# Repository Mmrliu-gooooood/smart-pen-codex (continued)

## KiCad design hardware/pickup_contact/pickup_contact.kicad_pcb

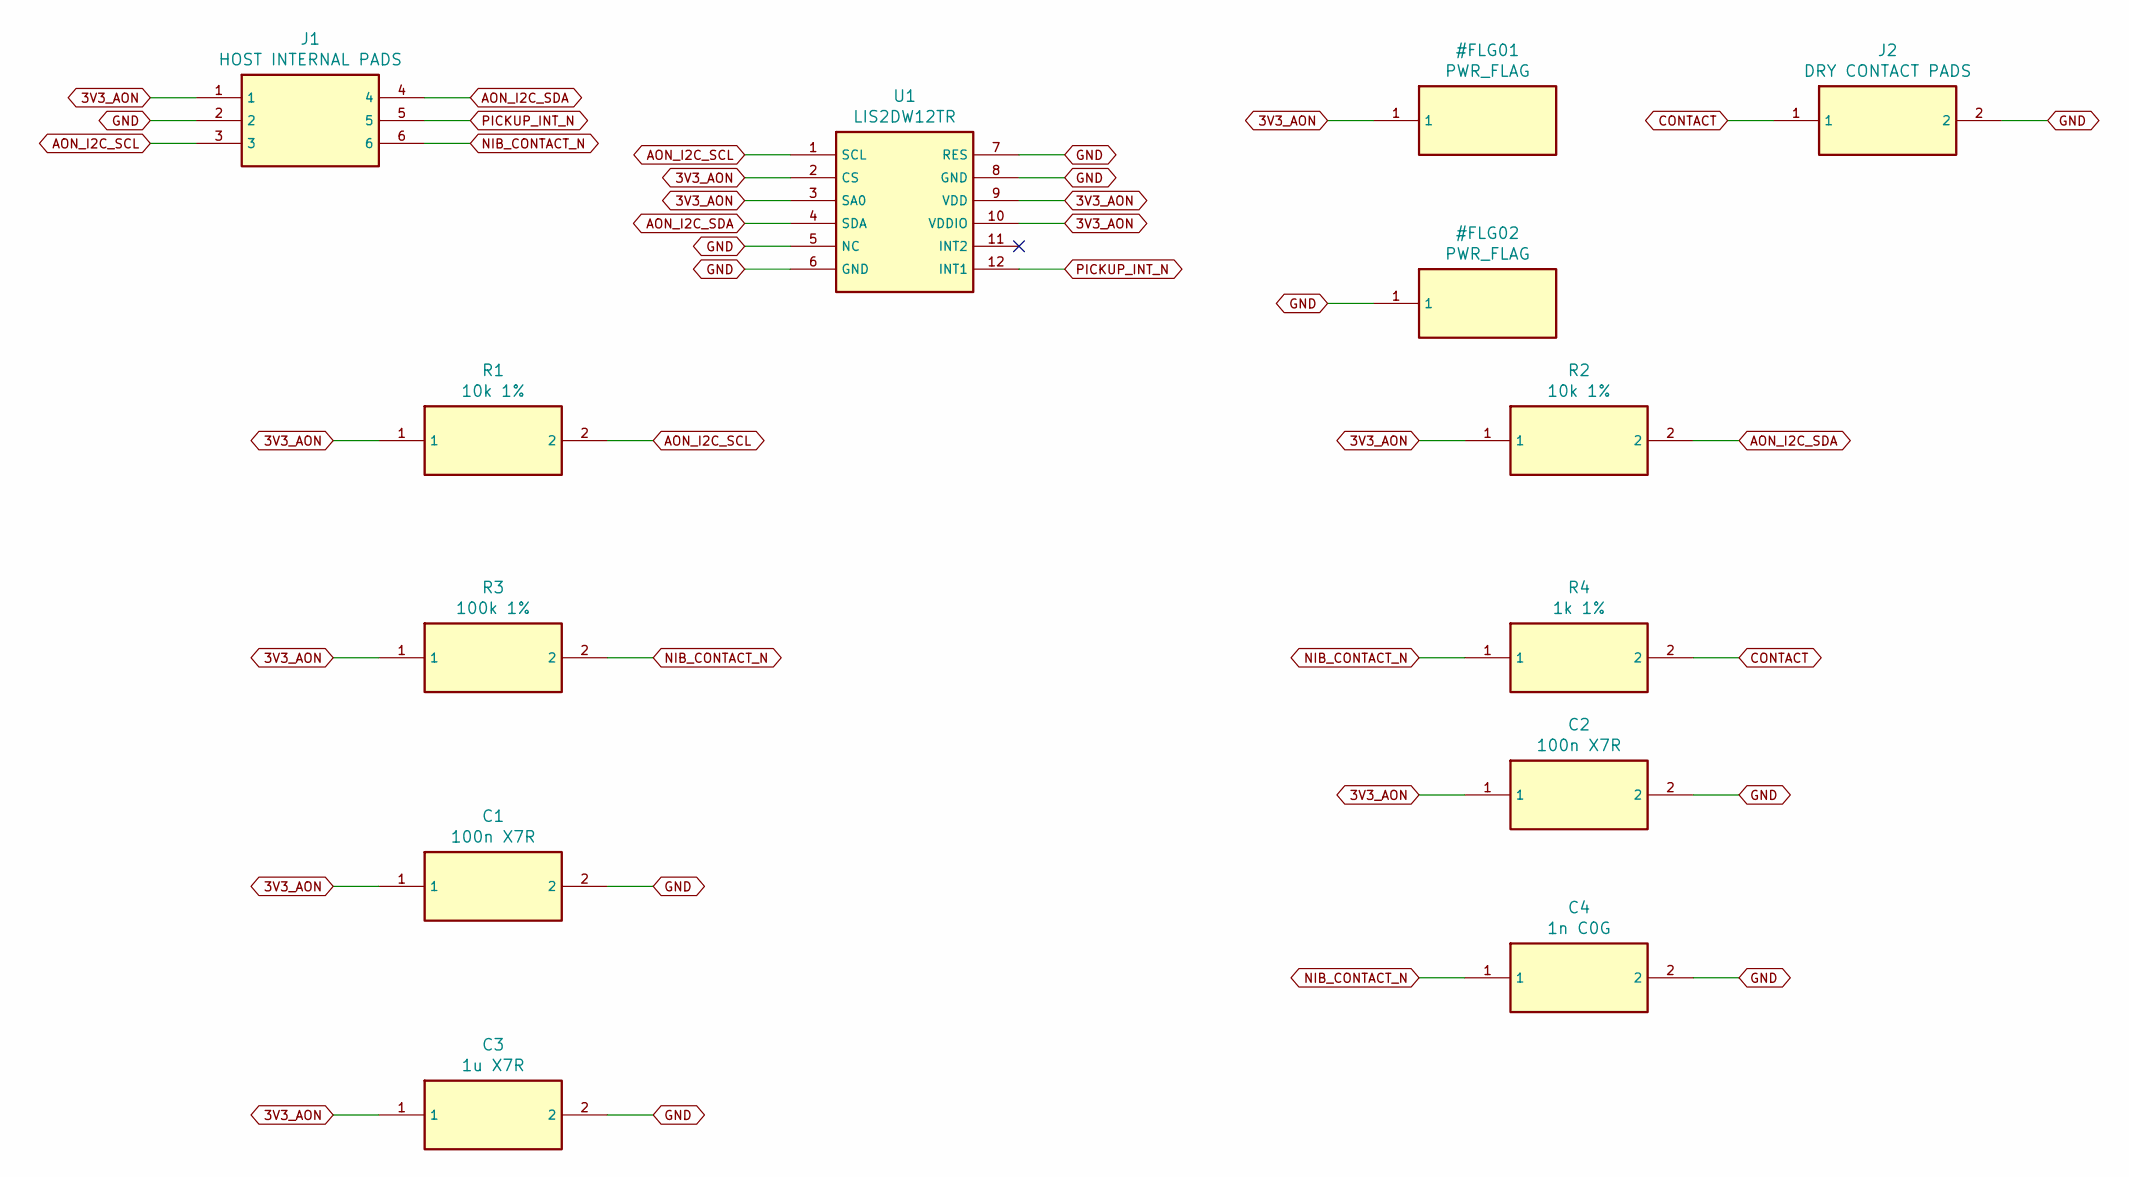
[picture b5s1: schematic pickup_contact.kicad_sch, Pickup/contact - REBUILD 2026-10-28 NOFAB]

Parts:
C1, C2: 100n X7R; C_0603_1608Metric
C3: 1u X7R; C_0603_1608Metric
C4: 1n C0G; C_0603_1608Metric
J1: HOST INTERNAL PADS; Host_6
J2: DRY CONTACT PADS; Contact_2
R1, R2: 10k 1%; R_0603_1608Metric
R3: 100k 1%; R_0603_1608Metric
R4: 1k 1%; R_0603_1608Metric
U1: LIS2DW12TR; LGA-12_2x2mm_P0.5mm

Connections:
3V3_AON: C1.1, C2.1, C3.1, J1.1, R1.1, R2.1, R3.1, U1.2 (CS), U1.3 (SA0), U1.9 (VDD), U1.10 (VDDIO)
AON_I2C_SCL: J1.3, R1.2, U1.1 (SCL)
AON_I2C_SDA: J1.4, R2.2, U1.4 (SDA)
CONTACT: J2.1, R4.2
GND: C1.2, C2.2, C3.2, C4.2, J1.2, J2.2, U1.5 (NC), U1.6 (GND), U1.7 (RES), U1.8 (GND)
NIB_CONTACT_N: C4.1, J1.6, R3.2, R4.1
PICKUP_INT_N: J1.5, U1.12 (INT1)

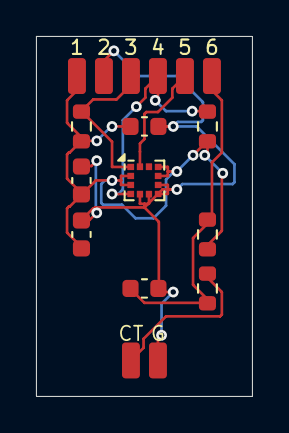
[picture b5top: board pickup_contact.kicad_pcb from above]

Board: 2 copper layers, 12.0 x 20.0 mm, 11 parts (0 on the bottom side), 7 nets.
